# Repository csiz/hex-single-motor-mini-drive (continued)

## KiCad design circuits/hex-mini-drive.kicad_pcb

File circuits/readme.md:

TODO for next circuit
---------------------

[ ] Maybe switch to a oscillation damping gate resistor of 3ohm. The AO4266E switching parameter uses 
Rgen = 3ohm, I think this is their recommended gate resistance.

[ ] Aaaargh, BOOT0 pin needs a pulldown resistor on the STM32G4!

[v] Think about connectors better. We should either drop or double down on USB-C. It would be very user friendly and the power delivery 
allows us to pick the 9-24V we need, but might be cumbersombe to control 24 devices. The SPI bus with slim connectors let's us keep it 
tight and in-house. Would we want a cheap single-sided board with USB-C and also a compact double sided assembly without USB at all.
... Let's go for double sided compact without USB, with the better stm32g4 with 5 opamps (so we can also ditch the opamp).
[v] USB-C footprint was correct with the cutouts. What we have now is incorrect!

[v] Need master circuit.
[v] Need flexi rotation I2C sensors.
[v] Via diameter was too small, should be at least 0.2/0.45

Need to implement in the new circuit
------------------------------------

Features of current version:
[v] Measure power line voltage.
[x] Re-pick voltage boost capacitor and resistor pair (using P FETS).
[v] Re-pick gate oscillation damping resistor for the inputs to the power MOSFET.
[v] Crystal oscilator and pick matching caps.
[v] Power regulator.
[v] USB-C connector maybe?
[v] Debugging connection with the trace line.
[v] 4 half bridge outputs
[v] 4 voltage inputs for the 4 outputs
[v] 1 voltage input for VCC
[v] 2 (preferably 4) current inputs from the 4 outputs; I chose 4.
[x] maybe 1 current input for total current. It would leave us with a floating ground which is iffy.
[v] SPI connection to main board. Not ~I2C~, it's too slow and consumes too much current. SPI will need
a chip select pin, but allows for parallel devices. SPI has hardware CRC calculation, seems useful.
[v] Spare I2C connection for the magnetic sensors.
[v] Status LED.

Lessons from previous version:
[x] Measure gate turn on characteristics of existing circuit...
[x] Maybe switch to a oscillation damping gate resistor of 3ohm. The AO4266E switching parameter uses 
Rgen = 3ohm, I think this is their recommended gate resistance.
[x] Definitely need to think about daisy chaining these, maybe use a signal buffer/transciever with an enable pin,
and/or mosfet switch for the chip power on. I2C to master board is probably the best and easiest way.
[v] Oopsies I flipped the sign of the V phase current measurement lines.
[x] The boost gate should maybe be connected to the driver side of the shunt resistor. At the moment we're measuring current used to charge the high gate.
[x] There's a summing option for the current measurments. Try outputing U, V, U+V, U+V+W using the 4th spare output.
[v] ! Think carefully about the shunt resistor placement, there's big interference going on if we measure during high side. Timing it around ground as
common mode voltage seems to fix it. Is that the only way to measure all current going through the motor coils?
[v] ! Measure voltage of the motor coils!
[x] There's a conflict between i2c and timer 3 channel 2. Choose a different GPIO for the red LED.
	I2C1 and TIM3_CH2 remapped
	Description
	When the following conditions are met:
	• I2C1 and TIM3 are clocked.
	• I/O port pin PB5 is configured as an alternate function output
	there is a conflict between the TIM3_CH2 signal and the I2C1 SMBA signal (even if SMBA is not used).
	In these cases the I/O port pin PB5 is set to 1 by default if the I/O alternate function output is selected and I2C1 is
	clocked. TIM3_CH2 cannot be used in output mode.
	Workaround
	To avoid this conflict, TIM3_CH2 can only be used in input mode.

[x] Double sided board. Not just yet.
[x] Drop voltage regulator and rely on master board for 3.3V; filter it though. We just needed to look for better 
components, there are cheap and small options that work well for us.
[x] Look for thinner IDC connector, and definitely SMD version for easier routing, use of space behind connector.
[v] Add voltage probes for the phase connectors so we can measure voltage both during driving and open connections.
We need to measure driving voltage to make sure our MOSFETS are turned on and giving us the voltage we command!
[v] Use Kelvin sense resistors (or pad hack) for the current measurement to avoid the unknown solder resistance.
https://www.analog.com/media/en/analog-dialogue/volume-46/number-2/articles/optimize-high-current-sensing-accuracy.pdf
[v] Don't drop the hall sensors, yet!
[v] The big problem with our measurements occurs when we switch from continuous 0 output from the low mosfet to mixed
output with the high mosfet. Any amount of mixed output seems to add an offset to our current measurement. Might be
worth putting the current sense only on the low mosfet branch.
[x] Choose a different mosfet driver to lower the minimum voltage under 5V. The undervoltage protection must be there
for a reason. Anyway, we chose 6V and up.
[v] Make it work with steppers... Neat!

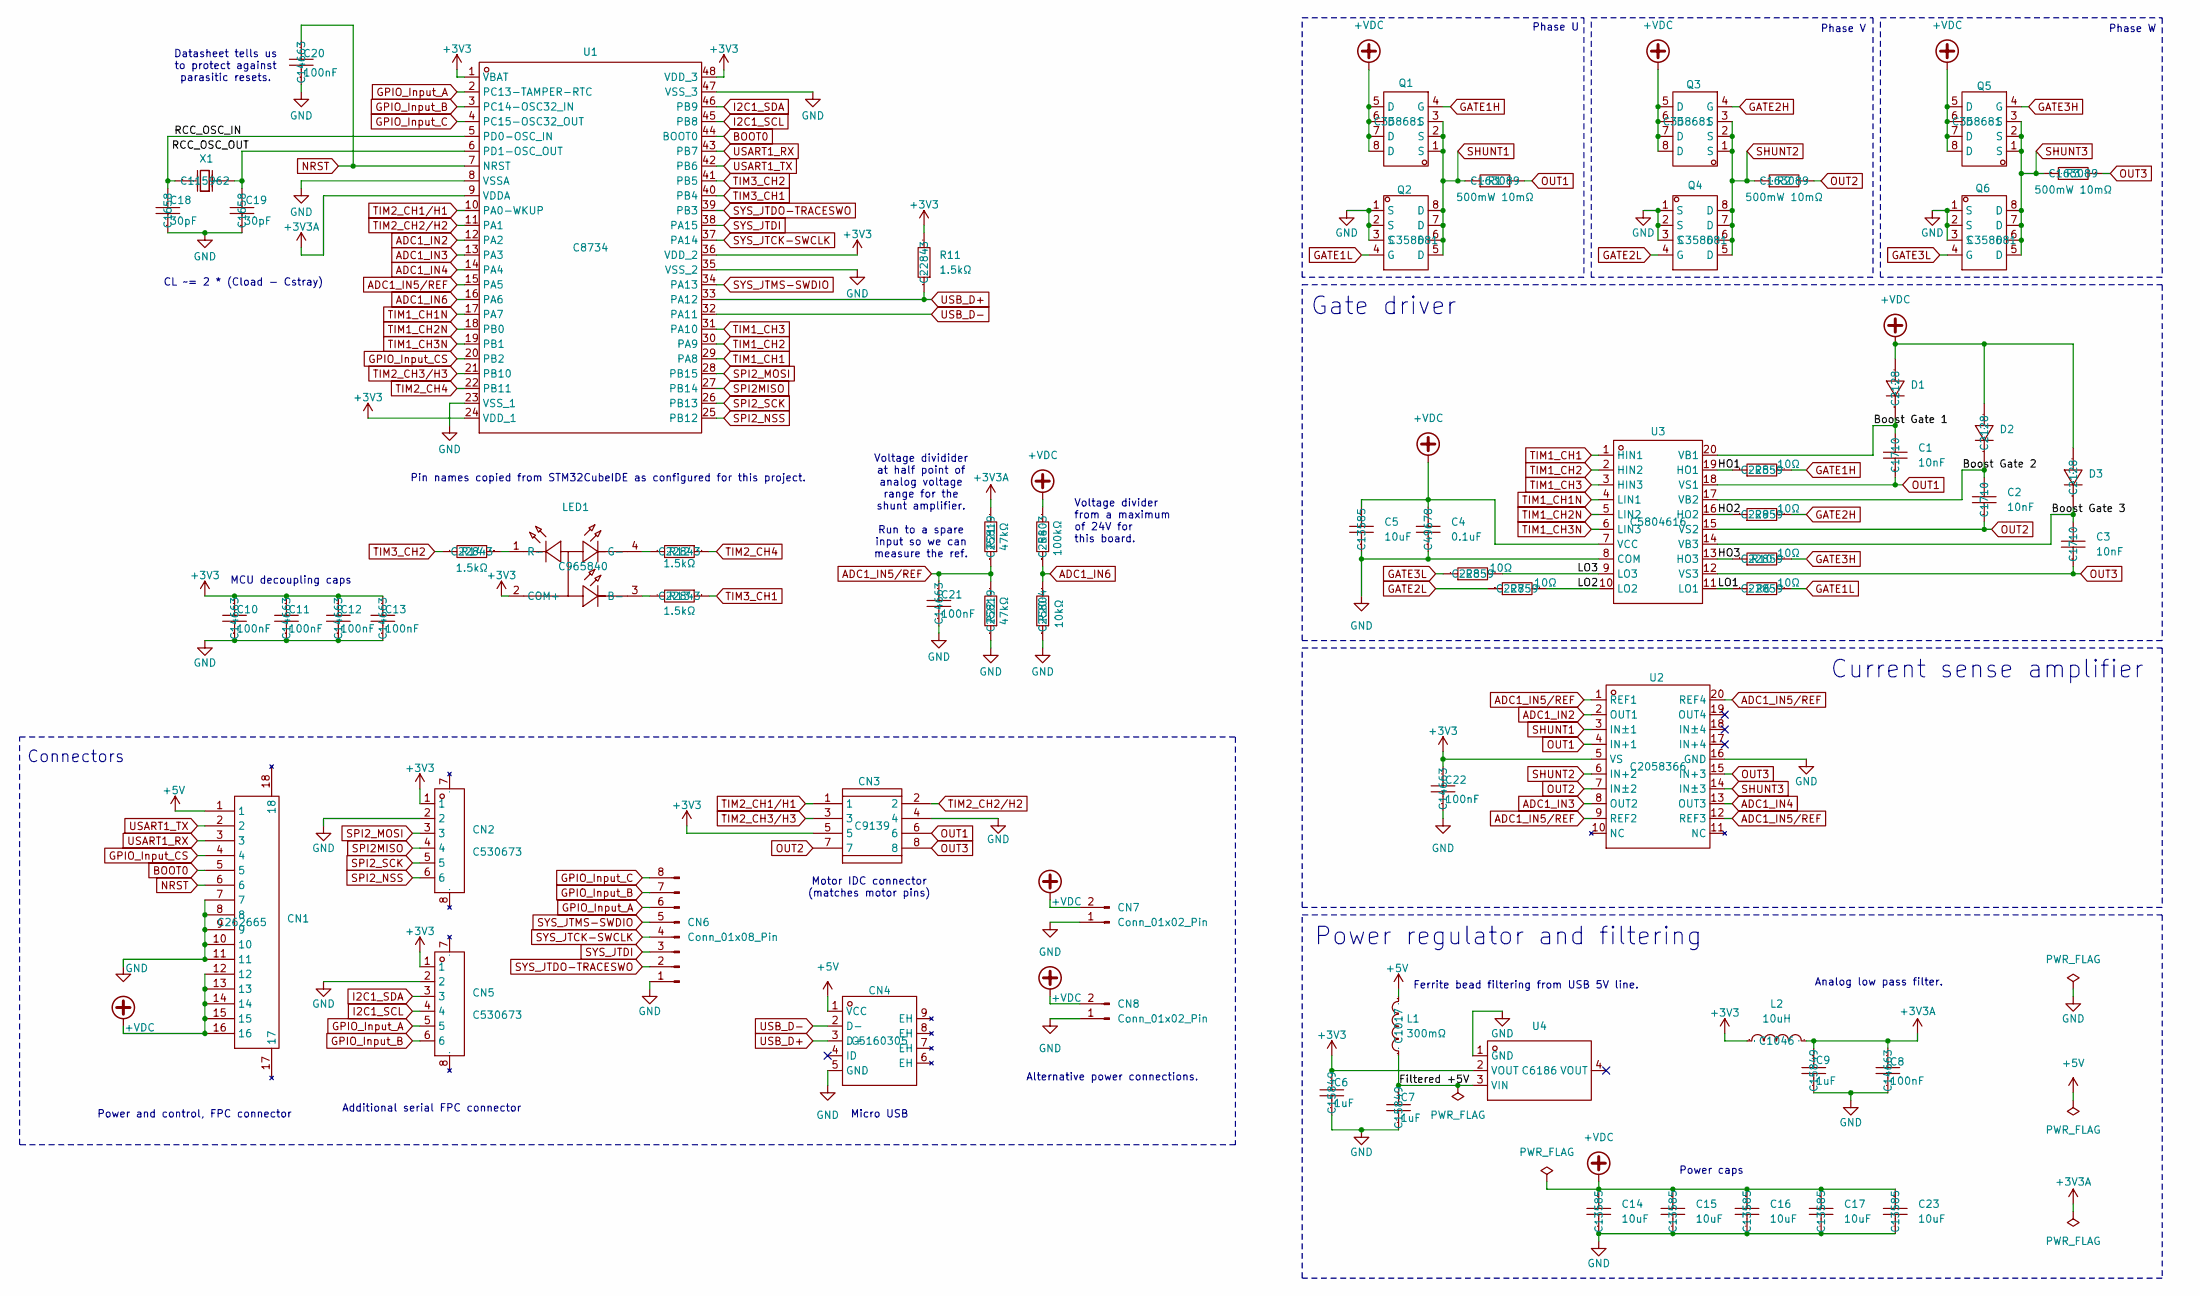
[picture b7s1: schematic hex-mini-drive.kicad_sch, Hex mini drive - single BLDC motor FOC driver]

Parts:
C1, C2, C3: 10nF; C0805; LCSC Part # C1710
C4: 0.1uF; C0805; LCSC Part # C49678
C5, C14, C15, C16, C17, C23: 10uF; C1206; LCSC Part # C13585
C6, C7, C9: 1uF; C0603; Manufacturer Part CL10A105KB8NNNC; LCSC Part Name 1uF ±10% 50V
C8, C10, C11, C12, C13, C20, C21, C22: 100nF; C0603; Manufacturer Part CC0603KRX7R9BB104; LCSC Part Name 100nF ±10% 50V
C18, C19: 30pF; C0603; Manufacturer Part 0603CG300J500NT; LCSC Part Name 30pF ±5% 50V
CN1: FPC-SMD_P0.50-16P_FGS-XJ-H2.0; Manufacturer Part AFC01-S16FCA-00; LCSC Part Name 间距:0.5mm P数:16P 翻盖式 下接
CN2, CN5: FPC-SMD_6P-P0.50_L3.8-W5.0; Manufacturer Part KH-0.5-H3.25-6PIN; LCSC Part Name 间距:0.5mm P数:6P 翻盖式 下接
CN3: IDC-TH_8P-P2.54-H-R2-C4-S2.54; LCSC Part # C9139
CN4: MICRO-USB-SMD_MICRONJ5P-1.0-1.25; LCSC Part # C5160305
CN6: Conn_01x08_Pin; PinHeader_1x08_P1.00mm_Vertical
CN7, CN8: Conn_01x02_Pin; PinHeader_1x02_P2.00mm_Vertical
D1, D2, D3: IN4148WS T4 SOD-323_L1.8-W1.3-LS2.5-RD; LCSC Part # C2128
L1: 300mΩ; L0805; Manufacturer Part GZ2012D601TF; LCSC Part Name 单路 0805磁珠 阻抗600Ω@100MHz
L2: 10uH; L0805; Manufacturer Part SDFL2012S100KTF; LCSC Part Name 10uH ±10%
LED1: LED-ARRAY-SMD_4P-L1.6-W1.5-BR_XL-1615RGBC-RF; Manufacturer Part XL-1615RGBC-RF; LCSC Part Name XL-1615RGBC-RF
Q1, Q2, Q3, Q4, Q5, Q6: AO4266E SOIC-8_L4.9-W3.9-P1.27-LS6.0-BL; LCSC Part # C358681
R1, R2, R3: 500mW 10mΩ; R0805; Manufacturer Part RLM10FTSMR010; LCSC Part Name 10mΩ ±1% 500mW
R4: 100kΩ; R0603; LCSC Part # C25803
R5, R6, R7, R8, R9, R10: 10Ω; R0603; Manufacturer Part 0603WAF100JT5E; LCSC Part Name 10Ω ±1% 100mW 厚膜电阻
R11, R12, R13, R14: 1.5kΩ; R0603; Manufacturer Part 0603WAF1501T5E; LCSC Part Name 1.5kΩ ±1% 100mW 厚膜电阻
R20: 10kΩ; R0603; LCSC Part # C25804
R21, R22: 47kΩ; R0603; LCSC Part # C25819
U1: STM32F103C8T6 LQFP-48_L7.0-W7.0-P0.50-LS9.0-BL; LCSC Part # C8734
U2: INA4181A1 TSSOP-20_L6.5-W4.4-P0.65-LS6.4-BL; LCSC Part # C2058366
U3: FD6288T TSSOP-20_L6.5-W4.4-P0.65-LS6.4-BL; LCSC Part # C5804616
U4: AMS1117-3.3 SOT-223-3_L6.5-W3.4-P2.30-LS7.0-BR; Manufacturer Part AMS1117-3.3; LCSC Part Name 输出3.3V 1A
X1: CRYSTAL-SMD_L5.0-W3.2; LCSC Part # C115962

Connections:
+3V3: C6.2, C10.2, C11.2, C12.2, C13.2, C22.2, CN2.1, CN3.5, CN5.1, L2.1, LED1.2 (COM+), R11.2, U1.1 (VBAT), U1.24 (VDD_1), U1.36 (VDD_2), U1.48 (VDD_3), U2.5 (VS), U4.2 (VOUT)
+3V3A: C8.2, C9.2, L2.2, R21.2, U1.9 (VDDA)
+5V: CN1.1, CN4.1 (VCC), L1.2
+VDC: C4.2, C5.2, C14.1, C15.1, C16.1, C17.1, C23.1, CN1.12, CN1.13, CN1.14, CN1.15, CN1.16, CN7.2, CN8.2, D1.2 (A), D2.2 (A), D3.2 (A), Q1.5 (D), Q1.6 (D), Q1.7 (D), Q1.8 (D), Q3.5 (D), Q3.6 (D), Q3.7 (D), Q3.8 (D), Q5.5 (D), Q5.6 (D), Q5.7 (D), Q5.8 (D), R4.2, U3.7 (VCC)
/Boost Gate 1: C1.2, D1.1 (K), U3.20 (VB1)
/Boost Gate 2: C2.2, D2.1 (K), U3.17 (VB2)
/Boost Gate 3: C3.2, D3.1 (K), U3.14 (VB3)
/Filtered +5V: C7.2, L1.1, U4.3 (VIN)
/HO1: R5.1, U3.19 (HO1)
/HO2: R9.1, U3.16 (HO2)
/HO3: R10.1, U3.13 (HO3)
/LO1: R6.1, U3.11 (LO1)
/LO2: R7.2, U3.10 (LO2)
/LO3: R8.2, U3.9 (LO3)
/RCC_OSC_IN: C18.2, U1.5 (PD0-OSC_IN), X1.1 (OSC1)
/RCC_OSC_OUT: C19.2, U1.6 (PD1-OSC_OUT), X1.2 (OSC2)
ADC1_IN2: U1.12 (PA2), U2.2 (OUT1)
ADC1_IN3: U1.13 (PA3), U2.8 (OUT2)
ADC1_IN4: U1.14 (PA4), U2.13 (OUT3)
ADC1_IN5/REF: C21.2, R21.1, R22.2, U1.15 (PA5), U2.1 (REF1), U2.9 (REF2), U2.12 (REF3), U2.20 (REF4)
ADC1_IN6: R4.1, R20.2, U1.16 (PA6)
BOOT0: CN1.5, U1.44 (BOOT0)
GATE1H: Q1.4 (G), R5.2
GATE1L: Q2.4 (G), R6.2
GATE2H: Q3.4 (G), R9.2
GATE2L: Q4.4 (G), R7.1
GATE3H: Q5.4 (G), R10.2
GATE3L: Q6.4 (G), R8.1
GND: C4.1, C5.1, C6.1, C7.1, C8.1, C9.1, C10.1, C11.1, C12.1, C13.1, C14.2, C15.2, C16.2, C17.2, C18.1, C19.1, C20.1, C21.1, C22.1, C23.2, CN1.7, CN1.8, CN1.9, CN1.10, CN1.11, CN2.2, CN3.4, CN4.5 (GND), CN5.2, CN6.1, CN7.1, CN8.1, Q2.1 (S), Q2.2 (S), Q2.3 (S), Q4.1 (S), Q4.2 (S), Q4.3 (S), Q6.1 (S), Q6.2 (S), Q6.3 (S), R20.1, R22.1, U1.8 (VSSA), U1.23 (VSS_1), U1.35 (VSS_2), U1.47 (VSS_3), U2.16 (GND), U3.8 (COM), U4.1 (GND)
GPIO_Input_A: CN5.5, CN6.6, U1.2 (PC13-TAMPER-RTC)
GPIO_Input_B: CN5.6, CN6.7, U1.3 (PC14-OSC32_IN)
GPIO_Input_C: CN6.8, U1.4 (PC15-OSC32_OUT)
GPIO_Input_CS: CN1.4, U1.20 (PB2)
I2C1_SCL: CN5.4, U1.45 (PB8)
I2C1_SDA: CN5.3, U1.46 (PB9)
NRST: C20.2, CN1.6, U1.7 (NRST)
unnamed: LED1.3 (B-), R13.2
unnamed: LED1.4 (G-), R12.2
unnamed: LED1.1 (R-), R14.1
OUT1: C1.1, CN3.6, R1.2, U2.4 (IN+1), U3.18 (VS1)
OUT2: C2.1, CN3.7, R2.2, U2.7 (IN±2), U3.15 (VS2)
OUT3: C3.1, CN3.8, R3.2, U2.15 (IN+3), U3.12 (VS3)
SHUNT1: Q1.1 (S), Q1.2 (S), Q1.3 (S), Q2.5 (D), Q2.6 (D), Q2.7 (D), Q2.8 (D), R1.1, U2.3 (IN±1)
SHUNT2: Q3.1 (S), Q3.2 (S), Q3.3 (S), Q4.5 (D), Q4.6 (D), Q4.7 (D), Q4.8 (D), R2.1, U2.6 (IN+2)
SHUNT3: Q5.1 (S), Q5.2 (S), Q5.3 (S), Q6.5 (D), Q6.6 (D), Q6.7 (D), Q6.8 (D), R3.1, U2.14 (IN±3)
SPI2MISO: CN2.4, U1.27 (PB14)
SPI2_MOSI: CN2.3, U1.28 (PB15)
SPI2_NSS: CN2.6, U1.25 (PB12)
SPI2_SCK: CN2.5, U1.26 (PB13)
SYS_JTCK-SWCLK: CN6.4, U1.37 (PA14)
SYS_JTDI: CN6.3, U1.38 (PA15)
SYS_JTDO-TRACESWO: CN6.2, U1.39 (PB3)
SYS_JTMS-SWDIO: CN6.5, U1.34 (PA13)
TIM1_CH1: U1.29 (PA8), U3.1 (HIN1)
TIM1_CH1N: U1.17 (PA7), U3.4 (LIN1)
TIM1_CH2: U1.30 (PA9), U3.2 (HIN2)
TIM1_CH2N: U1.18 (PB0), U3.5 (LIN2)
TIM1_CH3: U1.31 (PA10), U3.3 (HIN3)
TIM1_CH3N: U1.19 (PB1), U3.6 (LIN3)
TIM2_CH1/H1: CN3.1, U1.10 (PA0-WKUP)
TIM2_CH2/H2: CN3.2, U1.11 (PA1)
TIM2_CH3/H3: CN3.3, U1.21 (PB10)
TIM2_CH4: R12.1, U1.22 (PB11)
TIM3_CH1: R13.1, U1.40 (PB4)
TIM3_CH2: R14.2, U1.41 (PB5)
USART1_RX: CN1.3, U1.43 (PB7)
USART1_TX: CN1.2, U1.42 (PB6)
USB_D+: CN4.3 (D+), R11.1, U1.33 (PA12)
USB_D-: CN4.2 (D-), U1.32 (PA11)

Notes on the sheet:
Datasheet tells us to protect against parasitic resets.
Ferrite bead filtering from USB 5V line.
Additional serial FPC connector
Analog low pass filter.
Motor IDC connector (matches motor pins)
Gate driver
Micro USB
Voltage divider from a maximum of 24V for this board.
Phase U
Power regulator and filtering
Power caps
CL ~= 2 * (Cload - Cstray)
MCU decoupling caps
Voltage dividider at half point of analog voltage range for the shunt amplifier. Run to a spare input so we can measure the ref.
Connectors
Phase V
Power and control, FPC connector
Phase W
Current sense amplifier
Pin names copied from STM32CubeIDE as configured for this project.
Alternative power connections.

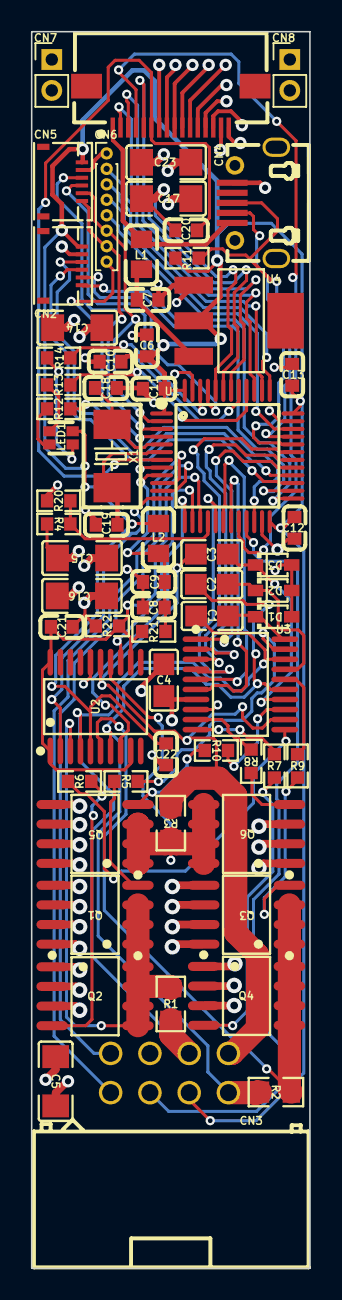
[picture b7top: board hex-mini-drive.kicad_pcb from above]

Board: 4 copper layers, 18.0 x 80.0 mm, 65 parts (0 on the bottom side), 69 nets.

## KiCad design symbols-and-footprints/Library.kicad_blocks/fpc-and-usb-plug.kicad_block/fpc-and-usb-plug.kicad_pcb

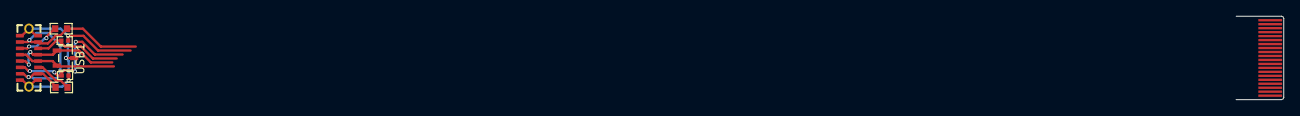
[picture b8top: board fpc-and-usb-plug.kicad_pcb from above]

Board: 2 copper layers, 7 parts (0 on the bottom side), 9 nets.

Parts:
D12: SOT-23-3_L3.0-W1.7-P0.95-LS2.9-BR
FPC1: FPC-20P-P0.50-Pattern
R17, R76: 56kΩ; R0603
R96, R103: 1MΩ; R0402
USB1: USB-C-SMD_TC-005

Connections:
/servo-usb-connector/CC1x: R76.1, USB1.A5 (CC1)
/servo-usb-connector/CC2x: R17.1, USB1.B5 (CC2)
/servo-usb-connector/VBUSx: R17.2, R76.2, USB1.A4 (VBUS), USB1.A9 (VBUS), USB1.B4 (VBUS), USB1.B9 (VBUS)
GND: D12.3 (K), FPC1.1, FPC1.2, FPC1.3, FPC1.4, FPC1.5, FPC1.6, FPC1.7, FPC1.8, FPC1.9, FPC1.10, R96.1, R103.1, USB1.1 (EH), USB1.2 (EH), USB1.A1 (GND), USB1.A12 (GND), USB1.B1 (GND), USB1.B12 (GND)
SERVO1_BOOT0: R96.2, USB1.A8 (SUB1)
SERVO1_NRST: R103.2, USB1.B8 (SUB2)
USBDN1_D+: D12.2 (A1), USB1.A6 (DP1), USB1.B6 (DP2)
USBDN1_D-: D12.1 (A1), USB1.A7 (DN1), USB1.B7 (DN2)
VCC: FPC1.11, FPC1.12, FPC1.13, FPC1.14, FPC1.15, FPC1.16, FPC1.17, FPC1.18, FPC1.19, FPC1.20

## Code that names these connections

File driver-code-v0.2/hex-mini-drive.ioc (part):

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Mcu.Name=STM32G431R(6-8-B)Tx
Mcu.Package=LQFP64
Mcu.UserName=STM32G431RBTx
PA0.Mode=IN1-Single-Ended
PA0.Signal=ADC1_IN1
PA1.Mode=PGA Internally connected_IO0_BIAS
PA1.Signal=OPAMP1_VINP
PA10.Signal=S_TIM1_CH3
PA11.Mode=Device
PA11.Signal=USB_DM
PA12.Mode=Device
PA12.Signal=USB_DP
PA13.Mode=Serial_Wire
PA13.Signal=SYS_JTMS-SWDIO
PA14.Mode=Serial_Wire
PA14.Signal=SYS_JTCK-SWCLK
PA15.Mode=NSS_Signal_Hard_Input
PA15.Signal=SPI3_NSS
PA2.Mode=IN3-Single-Ended
PA2.Signal=ADC1_IN3
PA3.Mode=PGA Internally connected_IO0_BIAS
PA3.Signal=OPAMP1_VINM0
PA4.Mode=IN17-Single-Ended
PA4.Signal=ADC2_IN17
PA5.Mode=PGA Internally connected_IO0_BIAS
PA5.Signal=OPAMP2_VINM0
PA6.Mode=IN3-Single-Ended
PA6.Signal=ADC2_IN3
PA7.Mode=PGA Internally connected_IO0_BIAS
PA7.Signal=OPAMP2_VINP
PA8.Mode=I2C
PA8.Signal=I2C2_SDA
PA9.Signal=S_TIM1_CH2
PB0.GPIOParameters=GPIO_ModeDefaultPP,GPIO_PuPd
PB0.GPIO_ModeDefaultPP=GPIO_MODE_AF_OD
PB0.GPIO_PuPd=GPIO_PULLUP
PB0.Signal=S_TIM3_CH3
PB1.Mode=IN12-Single-Ended
PB1.Signal=ADC1_IN12
PB10.Signal=S_TIM2_CH3
PB11.Mode=IN14-Single-Ended
PB11.Signal=ADC2_IN14
PB12.Mode=IN11-Single-Ended
PB12.Signal=ADC1_IN11
PB13.Mode=PGA Internally connected_IO0_BIAS
PB13.Signal=OPAMP3_VINP
PB14.GPIOParameters=GPIO_ModeDefaultPP,GPIO_PuPd
PB14.GPIO_ModeDefaultPP=GPIO_MODE_AF_PP
PB14.GPIO_PuPd=GPIO_NOPULL
PB14.Mode=PWM Generation2 CH2 CH2N
PB14.Signal=TIM1_CH2N
PB15.Mode=IN15-Single-Ended
PB15.Signal=ADC2_IN15
PB2.Mode=PGA Internally connected_IO0_BIAS
PB2.Signal=OPAMP3_VINM0
PB3.Mode=Full_Duplex_Slave
PB3.Signal=SPI3_SCK
PB4.Mode=Full_Duplex_Slave
PB4.Signal=SPI3_MISO
PB5.Signal=GPIO_Input
PB6.Signal=S_TIM4_CH1
PB7.Signal=S_TIM4_CH2
PB9.Mode=PWM Generation3 CH3 CH3N
PB9.Signal=TIM1_CH3N
PC0.Signal=S_TIM1_CH1
PC1.Mode=IN7-Single-Ended
PC1.Signal=ADC1_IN7
PC10.Mode=Asynchronous
PC10.Signal=USART3_TX
PC11.Mode=Asynchronous
PC11.Signal=USART3_RX
PC12.Mode=Full_Duplex_Slave
PC12.Signal=SPI3_MOSI
PC13.Mode=PWM Generation1 CH1 CH1N
PC13.Signal=TIM1_CH1N
PC14-OSC32_IN.Signal=GPIO_Input
PC15-OSC32_OUT.Signal=GPIO_Input
PC2.Mode=IN8-Single-Ended
PC2.Signal=ADC1_IN8
PC3.Signal=S_TIM1_CH4
PC4.Mode=I2C
PC4.Signal=I2C2_SCL
PC5.Mode=PWM Generation4 CH4 CH4N
PC5.Signal=TIM1_CH4N
PC6.GPIOParameters=GPIO_ModeDefaultPP,GPIO_PuPd
PC6.GPIO_ModeDefaultPP=GPIO_MODE_AF_OD
PC6.GPIO_PuPd=GPIO_PULLUP
PC6.Signal=S_TIM3_CH1
PC7.GPIOParameters=GPIO_ModeDefaultPP,GPIO_PuPd
PC7.GPIO_ModeDefaultPP=GPIO_MODE_AF_OD
PC7.GPIO_PuPd=GPIO_PULLUP
PC7.Signal=S_TIM3_CH2
PC8.Mode=I2C
PC8.Signal=I2C3_SCL
PC9.Mode=I2C
PC9.Signal=I2C3_SDA
PD2.Signal=GPIO_Input
PF0-OSC_IN.Mode=HSE-External-Oscillator
PF0-OSC_IN.Signal=RCC_OSC_IN
PF1-OSC_OUT.Mode=HSE-External-Oscillator
PF1-OSC_OUT.Signal=RCC_OSC_OUT
RCC.HSE_VALUE=16000000
RCC.SYSCLKFreq_VALUE=144000000
RCC.SYSCLKSource=RCC_SYSCLKSOURCE_PLLCLK
board=custom

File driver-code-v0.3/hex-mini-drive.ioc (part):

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Mcu.Name=STM32G431R(6-8-B)Tx
Mcu.Package=LQFP64
Mcu.UserName=STM32G431RBTx
PA0.Mode=IN1-Single-Ended
PA0.Signal=ADC1_IN1
PA12.Mode=PWM Generation2 CH2 CH2N
PA12.Signal=TIM1_CH2N
PA13.Mode=Serial_Wire
PA13.Signal=SYS_JTMS-SWDIO
PA14.Mode=Serial_Wire
PA14.Signal=SYS_JTCK-SWCLK
PA2.Mode=IN3-Single-Ended
PA2.Signal=ADC1_IN3
PA3.Mode=IN4-Single-Ended
PA3.Signal=ADC1_IN4
PA4.Mode=IN17-Single-Ended
PA4.Signal=ADC2_IN17
PA6.Mode=IN3-Single-Ended
PA6.Signal=ADC2_IN3
PA8.Mode=I2C
PA8.Signal=I2C2_SDA
PA9.Mode=I2C
PA9.Signal=I2C2_SCL
PB0.GPIOParameters=GPIO_ModeDefaultPP,GPIO_PuPd
PB0.GPIO_ModeDefaultPP=GPIO_MODE_AF_OD
PB0.GPIO_PuPd=GPIO_PULLUP
PB0.Signal=S_TIM3_CH3
PB11.Mode=IN14-Single-Ended
PB11.Signal=ADC2_IN14
PB12.Mode=NSS_Signal_Hard_Input
PB12.Signal=SPI2_NSS
PB13.Mode=Full_Duplex_Slave
PB13.Signal=SPI2_SCK
PB14.Mode=Full_Duplex_Slave
PB14.Signal=SPI2_MISO
PB15.Mode=Full_Duplex_Slave
PB15.Signal=SPI2_MOSI
PB3.Signal=S_TIM2_CH2
PB6.Signal=S_TIM4_CH1
PB7.Signal=S_TIM4_CH2
PB8-BOOT0.Signal=GPIO_Input
PB9.Mode=PWM Generation3 CH3 CH3N
PB9.Signal=TIM1_CH3N
PC0.Signal=S_TIM1_CH1
PC1.Signal=S_TIM1_CH2
PC10.Mode=Asynchronous
PC10.Signal=USART3_TX
PC11.Mode=Asynchronous
PC11.Signal=USART3_RX
PC13.Mode=PWM Generation1 CH1 CH1N
PC13.Signal=TIM1_CH1N
PC2.Signal=S_TIM1_CH3
PC3.Signal=S_TIM1_CH4
PC5.Mode=PWM Generation4 CH4 CH4N
PC5.Signal=TIM1_CH4N
PC6.GPIOParameters=GPIO_ModeDefaultPP,GPIO_PuPd
PC6.GPIO_ModeDefaultPP=GPIO_MODE_AF_OD
PC6.GPIO_PuPd=GPIO_PULLUP
PC6.Signal=S_TIM3_CH1
PC7.GPIOParameters=GPIO_ModeDefaultPP,GPIO_PuPd
PC7.GPIO_ModeDefaultPP=GPIO_MODE_AF_OD
PC7.GPIO_PuPd=GPIO_PULLUP
PC7.Signal=S_TIM3_CH2
PC8.Mode=I2C
PC8.Signal=I2C3_SCL
PC9.Mode=I2C
PC9.Signal=I2C3_SDA
PF0-OSC_IN.Mode=HSE-External-Oscillator
PF0-OSC_IN.Signal=RCC_OSC_IN
PF1-OSC_OUT.Mode=HSE-External-Oscillator
PF1-OSC_OUT.Signal=RCC_OSC_OUT
PG10-NRST.Signal=GPIO_Input
RCC.HSE_VALUE=16000000
RCC.SYSCLKFreq_VALUE=144000000
RCC.SYSCLKSource=RCC_SYSCLKSOURCE_PLLCLK
board=custom

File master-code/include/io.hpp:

#pragma once

#include "driver/gpio.h"
#include "driver/ledc.h"

// Red LED on the board, used as a status indicator.
const gpio_num_t status_led_pin = GPIO_NUM_35;

// SPI pins and related devices
// ----------------------------

// SPI3 data input.
const gpio_num_t spi3_miso_pin = GPIO_NUM_14;
// SPI3 data output.
const gpio_num_t spi3_mosi_pin = GPIO_NUM_9;
// SPI3 clock pin.
const gpio_num_t spi3_sclk_pin = GPIO_NUM_21;

// SPI2 data input.
const gpio_num_t spi2_miso_pin = GPIO_NUM_13;
// SPI2 data output.
const gpio_num_t spi2_mosi_pin = GPIO_NUM_11;
// SPI2 clock pin.
const gpio_num_t spi2_sclk_pin = GPIO_NUM_12;

// ### Display pins

// Display data pin (MOSI).
const gpio_num_t display_mosi = spi2_mosi_pin;
// Display clock pin.
const gpio_num_t display_sclk = spi2_sclk_pin;
// Display chip select pin.
const gpio_num_t display_cs   = GPIO_NUM_37;
// Display data/command pin.
const gpio_num_t display_dc   = GPIO_NUM_38;
// Display reset pin.
const gpio_num_t display_rst  = GPIO_NUM_18;

// Pin for touch screen interrupt.
const gpio_num_t touch_int_pin = GPIO_NUM_36;

// Shift register output enable pin (active low).
const gpio_num_t shift_oe = GPIO_NUM_47;


// ### Bank 1: Registers for chip select lines
// 
// Bank 1 of shift registers is a series of 3 8-bit shift registers used
// to control the chip select lines for the 24 motor driver circuits.

// Bank 1 data pin.
const gpio_num_t shift_bank1_data_in = spi3_mosi_pin;
// Bank 1 clock pin.
const gpio_num_t shift_bank1_clock = spi3_sclk_pin;
// Bank 1 latch pin.
const gpio_num_t shift_bank1_latch = GPIO_NUM_46;

// ### Bank 2: Registers for BOOT0/STOP and NRST lines, and extra outputs
// 
// Bank 2 of shift registers is a series of 7 8-bit shift registers used
// to control the BOOT0 and NRST lines for the 24 motor driver circuits.
// The 7th and last shift register is used for the following outputs:
// 1: I2C1_NRST
// 2: I2C1_BOOT0/STOP
// 3: I2C2_NRST
// 4: I2C2_BOOT0/STOP
// 5: USB sensor NRST
// 6: USB sensor BOOT0/STOP
// 7: Connect USB sensor to 5V supply.
// 8: Connect USB sensor to VCC supply.

// Bank 2 data pin.
const gpio_num_t shift_bank2_data_in = spi2_mosi_pin;
// Bank 2 clock pin.
const gpio_num_t shift_bank2_clock = spi2_sclk_pin;
// Bank 2 latch pin.
const gpio_num_t shift_bank2_latch = GPIO_NUM_45;

// ### SD card pins

// SD card command pin (CMD).
const gpio_num_t sd_cmd_pin = spi2_mosi_pin;
// SD card clock pin.
const gpio_num_t sd_clk_pin = spi2_sclk_pin;
// SD card data pin 0 (D0).
const gpio_num_t sd_data0_pin = spi2_miso_pin;
// SD card chip select pin.
const gpio_num_t sd_cs_pin = GPIO_NUM_10;

// I2C, USB and CAN bus pins
// -------------------------
// 
// I2C1 is connected to external connector 1.
// 
// I2C2 is connected to external connector 2, and the touch sensor, 
// and IMU sensor, and USB source controller (to control power supply for attached sensor device).

const gpio_num_t i2c1_sda_pin = GPIO_NUM_42;
const gpio_num_t i2c1_scl_pin = GPIO_NUM_41;

const gpio_num_t i2c2_scl_pin = GPIO_NUM_40;
const gpio_num_t i2c2_sda_pin = GPIO_NUM_39;

const gpio_num_t usb_dm_pin = GPIO_NUM_19;
const gpio_num_t usb_dp_pin = GPIO_NUM_20;

const gpio_num_t can_tx_pin = GPIO_NUM_1;
const gpio_num_t can_rx_pin = GPIO_NUM_2;


// Power control and monitoring pins
// ---------------------------------

const gpio_num_t vbus_voltage_pin = GPIO_NUM_4;
const gpio_num_t vbus_current_pin = GPIO_NUM_5;
const gpio_num_t connect_vbus_pin = GPIO_NUM_6;
const gpio_num_t connect_battery_pin = GPIO_NUM_7;
const gpio_num_t battery_current_pin = GPIO_NUM_15;
const gpio_num_t battery_voltage_pin = GPIO_NUM_16;

const gpio_num_t battery_1_pin = GPIO_NUM_17;
const gpio_num_t battery_2_pin = GPIO_NUM_48;

const gpio_num_t sensor_current_pin = GPIO_NUM_8;

const gpio_num_t boot0_pin = GPIO_NUM_0;

const gpio_num_t reference_pin = GPIO_NUM_3;


// Constants for attached IO devices
// ---------------------------------

const int display_width = 240;
const int display_height = 300;


// Initialize the PWM for the status LED.
void setup_status_led();

// Set the brightness of the status LED (0-255).
void set_status_led_brightness(uint8_t brightness);

// Initialize the SPI busses for the display, SD card, and shift registers.
void setup_spi_busses();

void setup_output_pins();

void enable_shift_register_outputs();

void disable_shift_register_outputs();

void setup_shift_register_bank1();

bool set_shift_register_bank1(uint8_t data[3]);

bool motor_spi_transaction(size_t motor_index, uint8_t* write_data, uint8_t* read_data, size_t length);

void setup_shift_register_bank2();

bool set_shift_register_bank2(uint8_t data[7]);

void connect_battery_to_vcc();

void disconnect_battery_from_vcc();

void connect_vbus_to_vcc();

void disconnect_vbus_from_vcc();

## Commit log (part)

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2025-08-06 Fix the PWM limiting logic.
2025-08-06 Rename alpha and beta to direct and quadrature because we skipped the Clarke transform.
2025-08-06 Add drive mode for target speed and position seeking via speed.
2025-08-09 Update webapp pages.
2025-08-09 Improve serialiser function naming.
2025-08-09 Gather the motor controller code under a new directory.
2025-08-09 Pass the controller explicitly instead of "this".
2025-08-09 Add the forgotten constants.
2025-08-11 Refactor the controller streaming code.
2025-08-11 Refactor the connection initialization code.
2025-08-11 Shorten sliders setup.
2025-08-11 Congregate control function and buttons.
2025-08-14 Refactor the monitor page to improve code reading flow.
2025-08-14 Connect multiple motors at the same time.
2025-08-18 Add another couple of control modes and improve some writing.
2025-08-18 Add parameter to flip rotation direction, move motor constant to main loop.
2025-08-19 Reintroduce the speed cap and round to nearest full rotation.
    We'll do better position seeking when we have more sensitivity and faster compute on the next PCB iteration.
2025-08-25 Reduce amount of data kept in memory.
2025-08-25 Gate the 3 phase control updates.
2025-10-06 Send phase resistance.
2025-10-06 Updata js libs.
2025-10-06 Begin new driver code project for v0.2, new chip, and we will copy code later.
2025-10-06 Begin new circuit design.
2025-10-10 Tentatively finish new schematic.
2025-10-13 Finish the new version schematic.
2025-10-14 Update electrical design rules.
2025-10-20 Near final v0.2 circuit design.
2025-10-21 Add a logo and finish circuit.
2025-10-21 Order v0.2 circuits.
2025-10-22 Update gitignore, don't ignore the circuit symbol library.
2025-10-22 Copy v0.2 to v0.3 to work on USB PD.
2025-10-29 Update circuit todo.
2025-11-10 Start code v0.3 with a slight variant of the stm32g4.
2025-11-10 Move/copy the symbols and footprints into a common library.
2025-11-10 Plugin rotation sensor for servos.
2025-11-10 Update schematic information panel.
2025-11-10 Make schematic for master circuit to control multiple servos.
2025-11-10 Sketch out v0.3 of the servo driver, without the USB port.
2025-11-12 Finish master controller circuit, arrange chips on the board.
2025-11-13 Partially wire up control circuit.
2025-11-14 Continue wiring control circuit.
2025-11-17 Almost wired controller.
2025-11-18 Complete wiring up control circuit (needs verifying).
2025-11-18 Finish the control circuit layout.
2025-11-20 Prepare the master circuit for manufacturing (fixed component placement and orientation).
2025-11-21 Fix sensors panel for production.
2025-11-24 Correction for sensor circuit.
2025-11-25 Start writing down procedure to switch to different stm32 mcu.
2025-11-25 Update gitignore to exclude builds.
2025-11-25 Generate initial code.
2025-11-25 Make new version compile a blank project.
2025-11-28 Setup for the STM32G4 and update the instructions.
2025-12-01 Test out the LED on driver v0.2.
2025-12-02 Copy driver code and modify until it compiles (wrong pinout!).
2025-12-03 Adapt code for new STM32, but we have the wrong chip selected in the CubeMX!
2025-12-03 Update CubeMX version.
2025-12-03 Switch to the correct chip version.
2025-12-06 Investigate why driver was restarting in a boot loop, we needed the pull-down on BOOT0 pin afterall.
2025-12-08 Restore USB comms.
2025-12-08 Update the PWM autoreload counter for the higher main frequency.
2025-12-09 Update the ADC timing and verify motor driver works again on the new version.
2025-12-15 Change systick to depend on TIM8.
2025-12-18 Reimplement USB buffering.
2025-12-18 Implement data transfer from interrupt through buffer.
2025-12-18 Fix off by 1 errors.
2025-12-18 Replace the buffer stuff with a flag.
2025-12-19 Turn the circular buffer into a class as it's used only from C++.
2025-12-19 Change the pwm frequency to 23.4KHz to have enough compute in the loop.
2025-12-20 Fix the stop button.
2025-12-22 Think about v0.3 driver circuit.
2025-12-22 Move all IO into a single header so we only need to modify one spot for different mcu.
2025-12-22 Update readme file for code transitions to new MCU..
2025-12-22 Move USB timeout logic into app_main code, fix write buffering.
2025-12-27 Start re-wiring v0.3 motor driver, 16mm width is too tight.
2025-12-29 Sketch out route for all crossing wires.
2025-12-29 Almost done wiring, but paths need refining.
2025-12-30 More circuit progress, there are ground islands, hmm.
2026-01-02 Optimized routing, but we need to go tighter.
2026-01-02 Thinned out the signal lines and tightened the layout, now to fit power caps.
2026-01-02 Finished v0.3 circuit layout.
2026-01-03 Fix positioning errors and realize SPI3 is not in the bootloader options.
2026-01-03 Sigh, SPI3 cannot be used for the bootloader, move to SPI2. Finish v0.3 again.
2026-01-04 Finalize v0.3 and generate production files.
2026-01-08 Compile and test master circuit for liveness. It lives!
2026-01-12 Test the screen using esp_lcd functions, much better than tft_espi for project sanity.
2026-01-13 Enable debugging over JTAG.
2026-01-14 Create agent instructions.
2026-01-14 Convert to esp-idf framework.
2026-01-14 Setup lvgl for graphics.
2026-01-14 Fix the config for 2MB of flash memory.
2026-01-14 Apparently the screen is 320 pixels tall instead of 280 like it says.
2026-01-15 Refactor code and split out gpio and display from main.
2026-01-19 Add custom partitions table and use max CPU frequency.
2026-01-19 Add qrcode dependency.
2026-01-19 Implement wifi with qrcode provisioning. Doesn't work tho...
2026-01-20 Redo provisioning using the esp ble app; they have the features exposed to make our own app on android or iphone.
2026-01-20 Simplify wifi code.
2026-01-20 Fix the watchdog timer issue.
2026-01-20 Enlarge the spiffs partition so we can load the whole web page.
2026-01-21 Try out a simple http server with mdns.
2026-01-21 Make it HTTPS.
2026-01-23 Forget v0.1 code, and ...
2026-01-23 ... make the v0.2 code active.
2026-01-23 Name the v0.1 circuit with the version tag.
2026-01-23 Remove a warning.
2026-01-27 Reimplement message framing using COBS.
2026-01-28 Try to fix serial port dropping bytes of data from USB, didn't work.
2026-01-30 We need a webworker to read the incoming data stream uninterrupted, or we silently lose data from the browser's buffer.
2026-02-02 Write the wire interface as a yaml file.
2026-02-02 Add interface comments into the spec.
2026-02-03 Describe the spec.
2026-02-03 Autogenerate C++ code with the struct definitions from the spec.
2026-02-03 Calculate size and write serialisation function declarations.
2026-02-03 Generate serialization implementation.
2026-02-03 Implement the generic seralisation functions.
2026-02-03 Copy over the cobs_encoding header.
2026-02-04 Generate javascript interface.
2026-02-04 Rename the previous index file and complete the js interface.
2026-02-04 Update the package to point to the generated build files.
2026-02-04 Add autogenerated notice.
2026-02-04 Repoint the include path to the dist directory so we capture the generated headers.
2026-02-09 Refactor the messaging interface to use the shared interface spec.
2026-03-06 Refactor code autogeneration.
2026-03-09 Add the interface to the esp32 code.
2026-03-10 Setup ws endpoint.
2026-03-11 Use snake_case.
2026-03-11 Define all the pins used in the circuit.
2026-03-26 Set all pin constants for the master board.
2026-03-27 Simplify main function.
2026-03-27 Unblock wifi provisioning so we don't trigger the watchdog.
2026-03-27 Ouch circuit got a bit spicy.
2026-03-29 Use the shift register outputs.
2026-03-31 Successfully connect vbus to vcc.
2026-03-31 Update dependencies.
2026-03-31 Also update the lock file.
2026-04-08 Sketch out SPI comms between esp32 and stm32. Replies are offset by a few bytes, hmm.
2026-04-08 Fix SPI comms for this circuit, we used the same spi line to also set the chip select pin...
    So we actually need to send the last 3 bytes to deassert all chip select lines.
2026-04-09 Turn on DMA for the SPI comms, now frequency works up to 10Mhz.
2026-04-13 Switch ESP IDF extension instead of platformio to remove an intermediary.
2026-04-13 Fix the ESP IDF version and make it work from the dockerfile.
2026-04-15 Refactor interface files to make them single file imports/includes.
2026-04-16 Refactor COBS buffer code, make a happy path for 0 padded messages.
2026-04-16 Fully reset the encoder buffers.
2026-04-17 Compile all cpp sources in the src folder.
2026-04-17 Extract the comms logic out of main.
2026-04-17 Define the maximum message size in the common interface.
2026-04-20 Reorganize the usb comms into a class so we can duplicate for spi.
2026-04-20 Incorporate the update function into the struct.
2026-04-23 Implement SPI interface between master controller and driver.
2026-04-27 Implement a passthrough interface between webapp - esp32 via wifi - to driver via SPI.
2026-04-27 Re-align JS and cpp interfaces.
2026-05-07 Make websocket messages async to gain a bit of speed.
2026-05-11 Pin wifi to core 0 and main loop on core 1.
2026-05-12 Split server and motor update tasks.
2026-05-12 Print all currently running tasks.
2026-05-12 Pin all floating tasks to core 0.
2026-05-12 Update mdns dependency.
2026-05-15 Optimize wifi messages.
2026-05-18 Switch to SPI polling transmit.
2026-05-18 Increase SPI transaction size to make better use of throughput.
2026-05-22 Attempt to compile v0.3 driver code.
2026-05-25 Add choice between usb and wifi connections.
2026-05-28 Adapt driver code for v0.3 .
2026-05-29 This version seems to work a bit better if we remove the common sum offset.
2026-05-29 Fix some js serialization errors.
2026-05-29 Remove unused linker scripts.
2026-05-29 Make driver v0.3 the main code and replace driver-code-v0.2.
2026-05-29 Copy v0.3 as starting point for v0.4
2026-05-29 Convert to kicad 10.
2026-05-29 Fix LED pwm setting, now green light works.
2026-05-29 Begin the v0.4 driver code.
2026-06-01 Make schematic for v0.4 driver circuit.
2026-06-03 Almost done re-wiring v0.4
2026-06-03 Add autosave file to gitignore.
2026-06-03 Tentatively done wiring v0.4.
2026-06-03 Finish and generate production files for v0.4 driver circuit.
2026-06-04 Update circuit gitignore.
2026-06-04 Rename master circuit to v0.1.
2026-06-04 Duplicate master circuit to start v0.2.
2026-06-11 Working on new circuit.
2026-06-16 Almost complete new master circuit schematic.
2026-06-17 Drop unused features and arrange components on new master circuit board.
2026-06-18 Connect one of the USB outputs, outline part placement.
2026-06-18 Design block experimentation.
2026-06-19 Deal with most of the connection spider web, connector lines remaining.
2026-06-22 USB hub lines remaining.
2026-06-22 Finish wiring master circuit v0.2.
2026-06-23 Make schematic for the cable plug and extension circuit.
2026-06-26 Working on rally compact layout for cable extender.
2026-06-26 Sketch out output paths.
2026-06-29 Work on cable outline, and almost finish wiring.
2026-06-30 Finish extender cable circuit.
